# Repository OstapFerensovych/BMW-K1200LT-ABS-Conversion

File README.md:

# BMW K1200LT iABS to iABS gen 2 Conversion PCB and Firmware.

To retrofit BMW K1200LT motorcycle we used the ATE/Teves iABS-II module from 2010 R1200GS K25.  
iABS-II uses CAN bus to communicate with ZFE, DME modules in the original R1200GS schematic.  

This project is developed to provide K1200LT necessary signals from ATE/Teves iABS-II CAN bus:
- Speed signal for K1200LT dash
- Brake and tail lights output
- ABS warning LED output
- General warning LED output  

<!-- 

 -->

## Other resources. 
[Shematics](docs/)

#### PCB is designed in KiCAD 5.1.9

## License

MIT

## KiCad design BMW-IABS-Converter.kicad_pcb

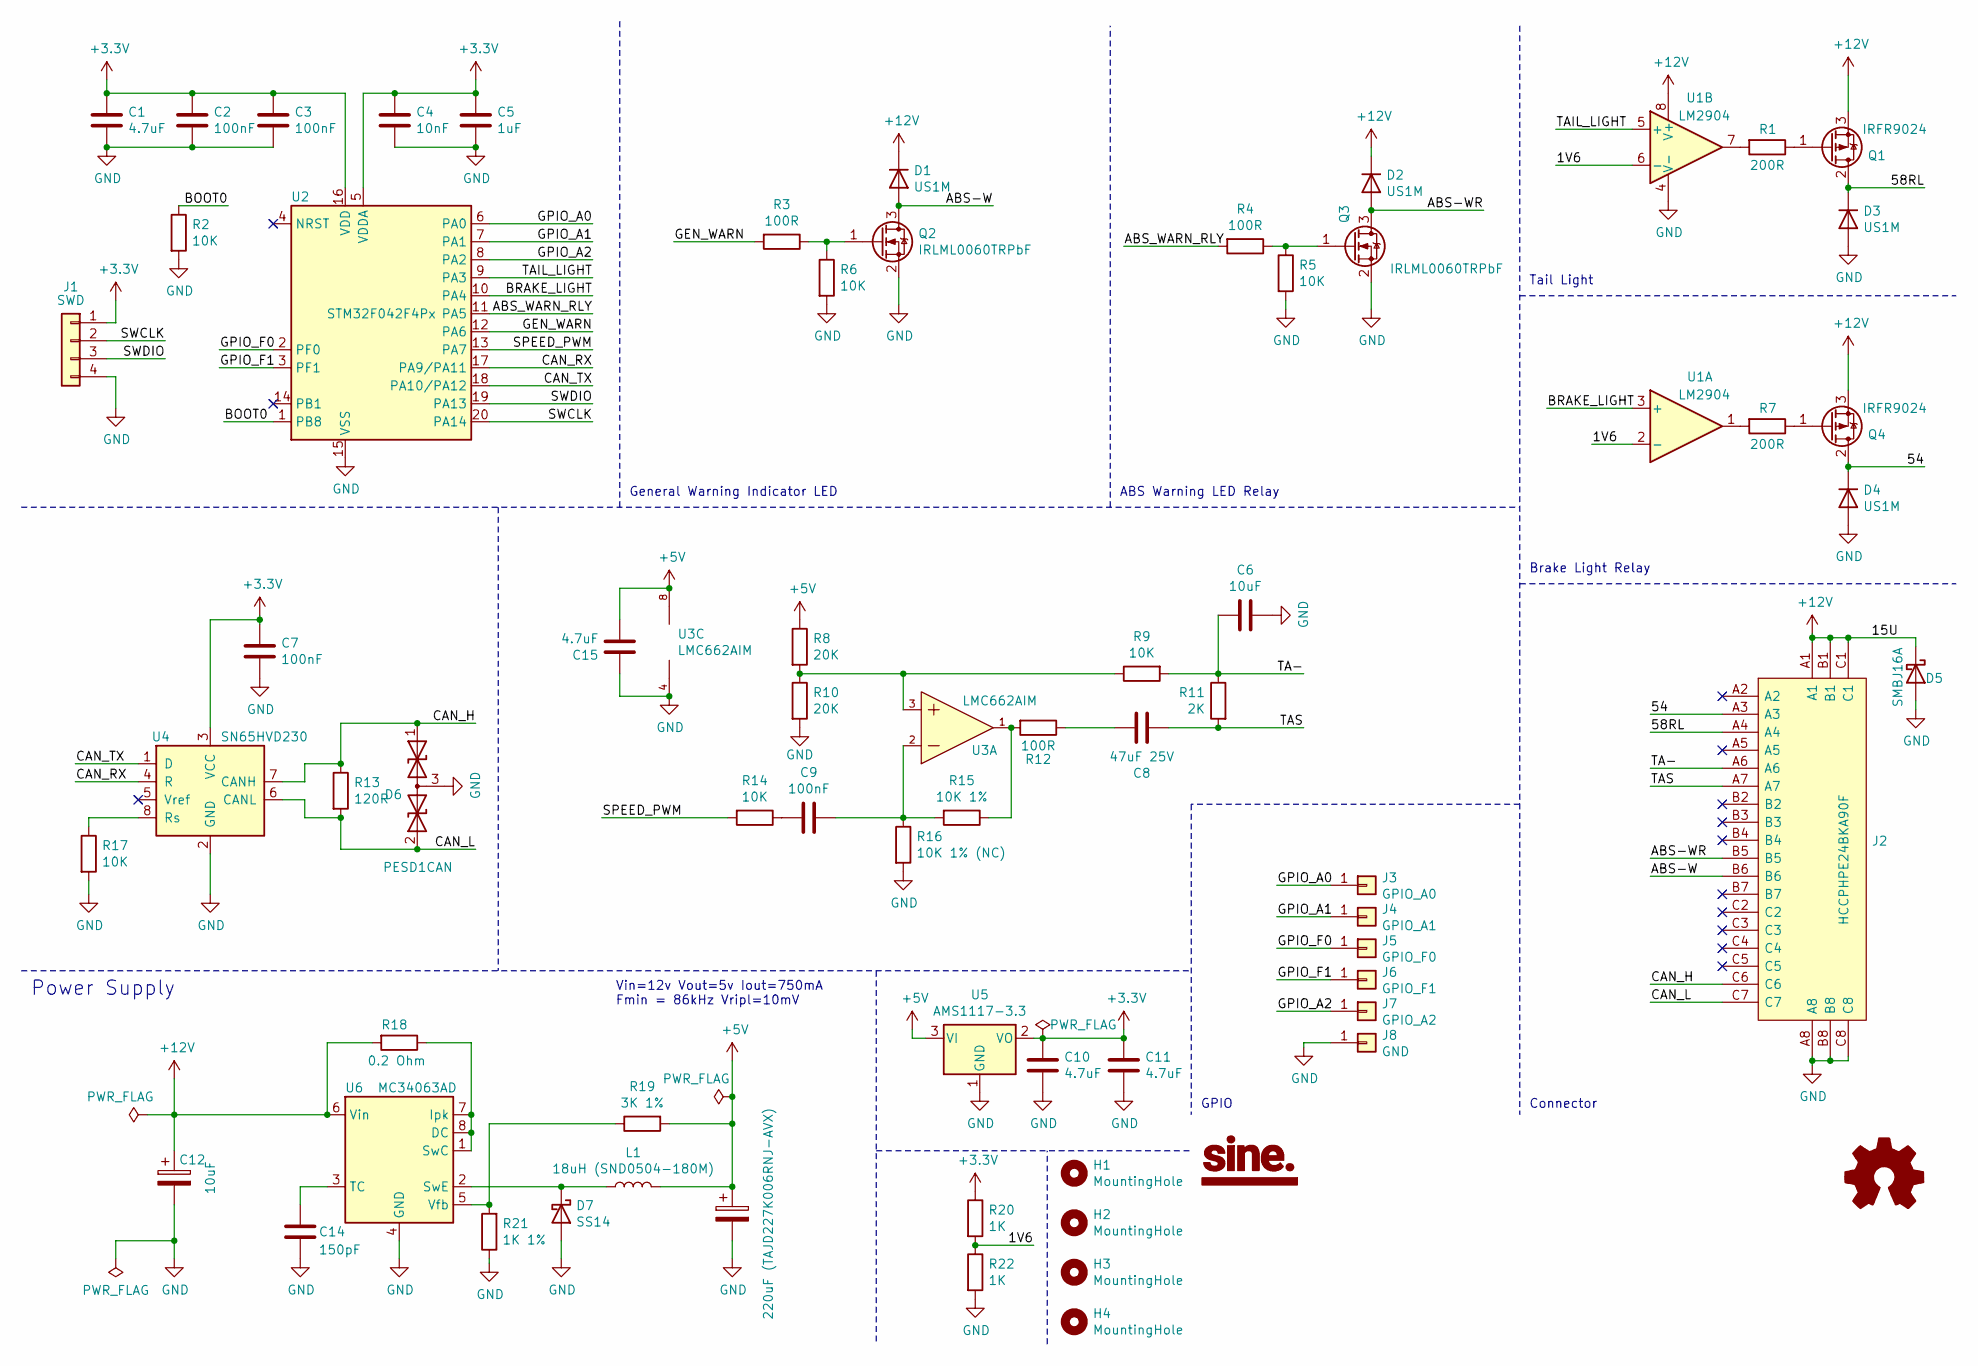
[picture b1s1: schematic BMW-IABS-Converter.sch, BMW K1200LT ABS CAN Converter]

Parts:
C1, C10, C11, C15: 4.7uF; C_0805_2012Metric
C2, C3, C7, C9: 100nF; C_0402_1005Metric
C4: 10nF; C_0402_1005Metric
C5: 1uF; C_0603_1608Metric
C6: 10uF; C_0805_2012Metric
C8: 47uF 25V; C_Radial_D6.3mm_H11.0mm_P2.50mm
C12: 10uF; C_1206_3216Metric
C13: 220uF (TAJD227K006RNJ-AVX); CP_EIA-7343-31_Kemet-D
C14: 150pF; C_0402_1005Metric
D1, D2, D3, D4: US1M; D_SMA
D5: SMBJ16A; D_SMB
D6: PESD1CAN; SOT-23
D7: SS14; D_SMA
H1, H2, H3, H4: MountingHole; MountingHole_3.2mm_M3
J1: SWD; PinHeader_1x04_P2.54mm_Vertical
J2: HCCPHPE24BKA90F; Manufacturer_Part_Number HCCPHPE24BKA90F
J3: GPIO_A0; PinHeader_1x01_P1.27mm_Vertical
J4: GPIO_A1; PinHeader_1x01_P1.27mm_Vertical
J5: GPIO_F0; PinHeader_1x01_P1.27mm_Vertical
J6: GPIO_F1; PinHeader_1x01_P1.27mm_Vertical
J7: GPIO_A2; PinHeader_1x01_P1.27mm_Vertical
J8: GND; PinHeader_1x01_P1.27mm_Vertical
L1: 18uH (SND0504-180M); L_Wuerth_WE-PD2-Typ-MS
LOGO1: Sine_Logo_S; sine_logo_small
LOGO2: Logo_Open_Hardware_Small; OSHW-Symbol_6.7x6mm_SilkScreen
Q1, Q4: IRFR9024; TO-252-2
Q2, Q3: IRLML0060TRPbF; SOT-23
R1, R7: 200R; R_0603_1608Metric
R2, R5, R6, R14, R17: 10K; R_0402_1005Metric
R3, R4, R12: 100R; R_0402_1005Metric
R8, R10: 20K; R_0603_1608Metric
R9: 10K; R_1206_3216Metric
R11: 2K; R_1206_3216Metric
R13: 120R; R_0603_1608Metric
R15: 10K 1%; R_0402_1005Metric
R16: 10K 1% (NC); R_0402_1005Metric
R18: 0.2 Ohm; R_0603_1608Metric
R19: 3K 1%; R_0603_1608Metric
R20, R22: 1K; R_0805_2012Metric
R21: 1K 1%; R_0603_1608Metric
U1: LM2904; SOIC-8_3.9x4.9mm_P1.27mm
U2: STM32F042F4Px; TSSOP-20_4.4x6.5mm_P0.65mm
U3: LMC662AIM; SOIC-8_3.9x4.9mm_P1.27mm
U4: SN65HVD230; SOIC-8_3.9x4.9mm_P1.27mm
U5: AMS1117-3.3; SOT-223-3_TabPin2
U6: MC34063AD; SOIC-8_3.9x4.9mm_P1.27mm

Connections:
+3V3: C1.1, C2.1, C3.1, C4.1, C5.1, C7.1, C10.1, C11.1, J1.1, R20.1, U2.5 (VDDA), U2.16 (VDD), U4.3 (VCC), U5.2 (VO)
+5V: C13.1, C15.2, L1.2, R8.1, R19.2, U3.8 (V+), U5.3 (VI)
+12V: C12.1, D1.1 (K), D2.1 (K), D5.1 (K), J2.A1, J2.B1, J2.C1, Q1.3 (S), Q4.3 (S), R18.2, U1.8 (V+), U6.6 (Vin)
/1V6: R20.2, R22.1, U1.2 (-), U1.6 (-)
/54: D4.1 (K), J2.A3, Q4.2 (D)
/58RL: D3.1 (K), J2.A4, Q1.2 (D)
/ABS-W: D1.2 (A), J2.B6, Q2.3 (D)
/ABS-WR: D2.2 (A), J2.B5, Q3.3 (D)
/ABS_WARN_RLY: R4.2, U2.11 (PA5)
/BOOT0: R2.1, U2.1 (PB8)
/BRAKE_LIGHT: U1.3 (+), U2.10 (PA4)
/CAN_H: D6.1 (A1), J2.C6, R13.1, U4.7 (CANH)
/CAN_L: D6.2 (A2), J2.C7, R13.2, U4.6 (CANL)
/CAN_RX: U2.17 (PA9/PA11), U4.4 (R)
/CAN_TX: U2.18 (PA10/PA12), U4.1 (D)
/GEN_WARN: R3.2, U2.12 (PA6)
/GPIO_A0: J3.1, U2.6 (PA0)
/GPIO_A1: J4.1, U2.7 (PA1)
/GPIO_A2: J7.1, U2.8 (PA2)
/GPIO_F0: J5.1, U2.2 (PF0)
/GPIO_F1: J6.1, U2.3 (PF1)
/SPEED_PWM: R14.2, U2.13 (PA7)
/SWCLK: J1.2, U2.20 (PA14)
/SWDIO: J1.3, U2.19 (PA13)
/TA-: C6.2, J2.A6, R9.2, R11.1
/TAIL_LIGHT: U1.5 (+), U2.9 (PA3)
/TAS: C8.1, J2.A7, R11.2
GND: C1.2, C2.2, C3.2, C4.2, C5.2, C6.1, C7.2, C10.2, C11.2, C12.2, C13.2, C14.2, C15.1, D3.2 (A), D4.2 (A), D5.2 (A), D6.3 (common), D7.2 (A), J1.4, J2.A8, J2.B8, J2.C8, J8.1, Q2.2 (S), Q3.2 (S), R2.2, R5.2, R6.2, R10.2, R16.2, R17.2, R21.1, R22.2, U1.4 (V-), U2.15 (VSS), U3.4 (V-), U4.2 (GND), U5.1 (GND), U6.4 (GND)
unnamed: C8.2, R12.1
unnamed: C9.1, R15.2, R16.1, U3.2 (INA-)
unnamed: C9.2, R14.1
unnamed: C14.1, U6.3 (TC)
unnamed: D7.1 (K), L1.1, U6.2 (SwE)
unnamed: Q1.1 (G), R1.1
unnamed: Q2.1 (G), R3.1, R6.1
unnamed: Q3.1 (G), R4.1, R5.1
unnamed: Q4.1 (G), R7.1
unnamed: R1.2, U1.7
unnamed: R7.2, U1.1
unnamed: R8.2, R9.1, R10.1, U3.3 (INA+)
unnamed: R12.2, R15.1, U3.1 (OUTA)
unnamed: R17.1, U4.8 (Rs)
unnamed: R18.1, U6.1 (SwC), U6.7 (Ipk), U6.8 (DC)
unnamed: R19.1, R21.2, U6.5 (Vfb)

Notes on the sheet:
Power Supply
Vin=12v Vout=5v Iout=750mA Fmin = 86kHz Vripl=10mV
ABS Warning LED Relay
General Warning Indicator LED
Brake Light Relay
Tail Light
Connector
GPIO

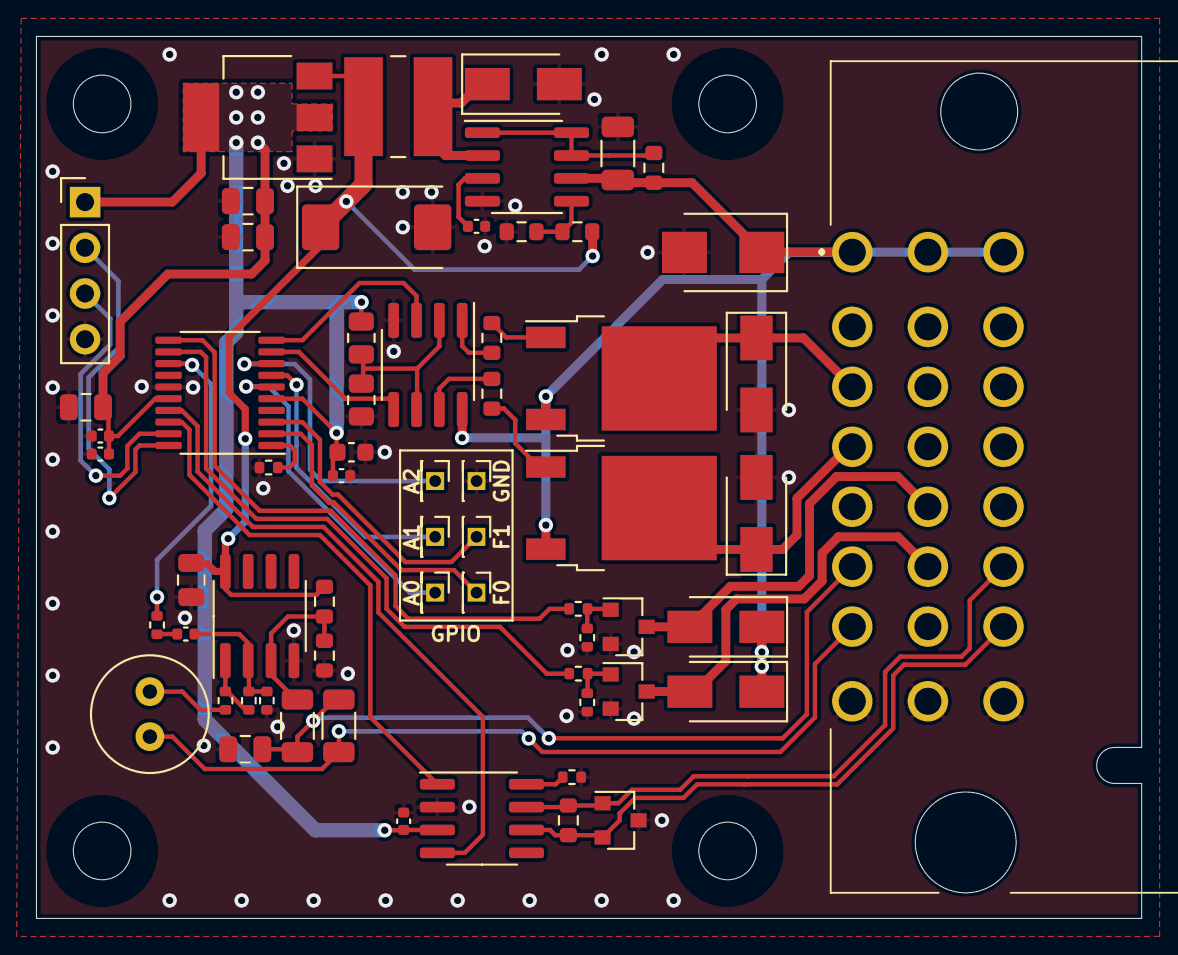
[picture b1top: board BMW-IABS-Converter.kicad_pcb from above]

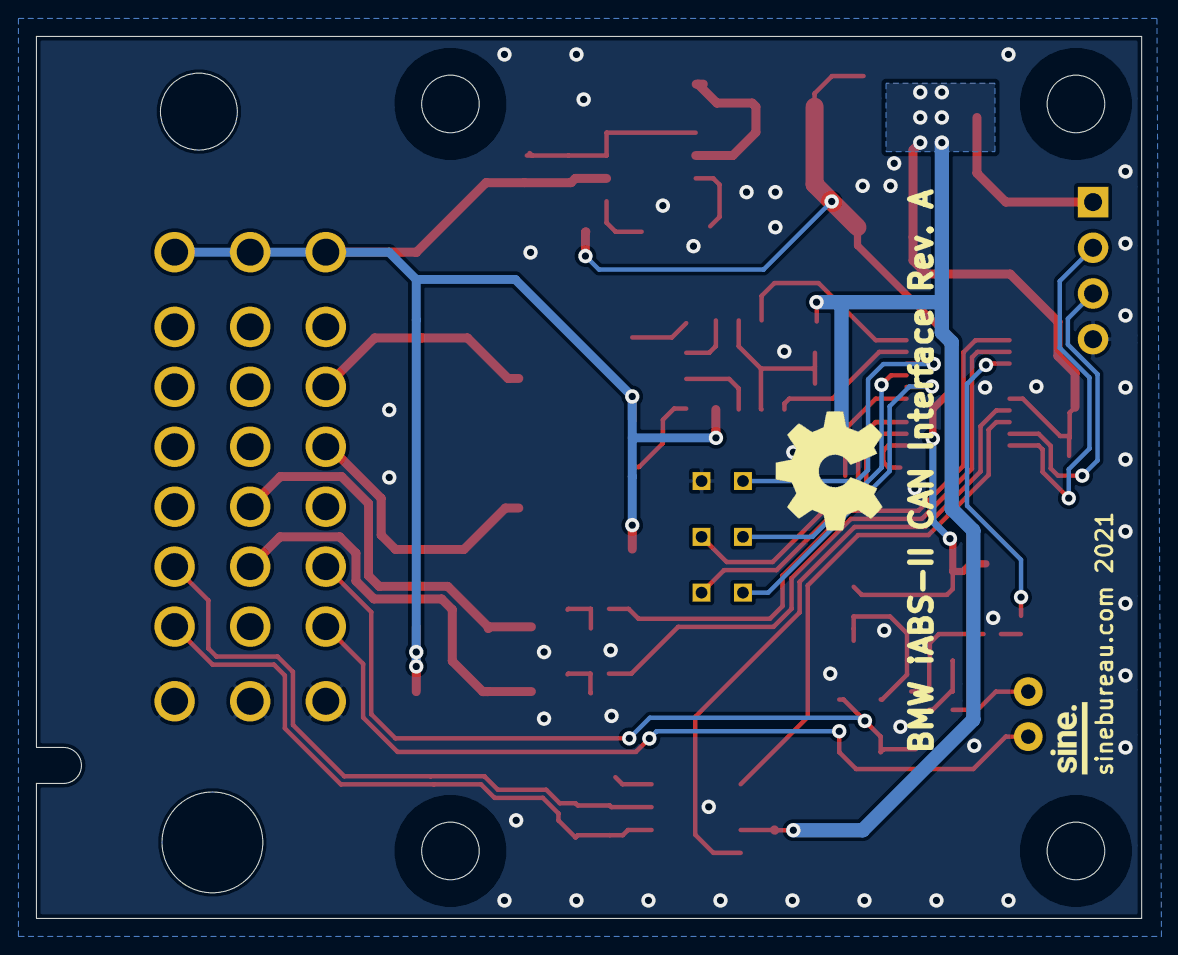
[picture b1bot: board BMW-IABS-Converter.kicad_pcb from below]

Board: 2 copper layers, 61.4 x 49.0 mm, 69 parts (2 on the bottom side), 44 nets.

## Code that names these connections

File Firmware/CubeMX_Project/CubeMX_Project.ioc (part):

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Mcu.Name=STM32F042F4Px
Mcu.Package=TSSOP20
Mcu.UserName=STM32F042F4Px
PA0.Signal=GPIO_Output
PA1.Signal=GPIO_Output
PA11.Mode=CAN_Activate
PA11.Signal=CAN_RX
PA12.Mode=CAN_Activate
PA12.Signal=CAN_TX
PA13.Mode=Serial_Wire
PA13.Signal=SYS_SWDIO
PA14.Mode=Serial_Wire
PA14.Signal=SYS_SWCLK
PA2.Signal=GPIO_Output
PA3.GPIOParameters=GPIO_Label
PA3.GPIO_Label=Tail_light
PA3.Signal=GPIO_Output
PA4.GPIOParameters=GPIO_Label
PA4.GPIO_Label=Brake_light
PA4.Signal=GPIO_Output
PA5.GPIOParameters=GPIO_Label
PA5.GPIO_Label=ABS_Warn_RLY
PA5.Signal=GPIO_Output
PA6.GPIOParameters=GPIO_Label
PA6.GPIO_Label=Gen_warn
PA6.Signal=GPIO_Output
PA7.GPIOParameters=GPIO_Label
PA7.GPIO_Label=Speedo
PA7.Signal=S_TIM3_CH2
PF0-OSC_IN.Signal=GPIO_Output
PF1-OSC_OUT.Signal=GPIO_Output
board=custom

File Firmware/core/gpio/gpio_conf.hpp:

#pragma once
#include "gpio.hpp"

enum class line {
    __invalid__,
    can_rx,
    can_tx,
    speedo,
    gen_warn,
    abs_warn_relay,
    brake_lights,
    tail_lights,
    gpio_A0,
    gpio_A1,
    gpio_A2,
    gpio_F0,
    gpio_F1
};

// clang-format off
constexpr std::pair<line, gpio::pin_config> pins_config[] = {
    {line::can_rx,         {gpio::port::a, 11, 0, gpio::mode::af_io, gpio::drive::push_pull, gpio::speed::high, gpio::pull::none, gpio::alt_func::af4}},
    {line::can_tx,         {gpio::port::a, 12, 0, gpio::mode::af_io, gpio::drive::push_pull, gpio::speed::high, gpio::pull::none, gpio::alt_func::af4}},
    {line::speedo,         {gpio::port::a, 7, 0,  gpio::mode::af_io,  gpio::drive::push_pull, gpio::speed::high, gpio::pull::none, gpio::alt_func::af1 }},
    {line::gen_warn,       {gpio::port::a, 6, 0,  gpio::mode::gp_out,  gpio::drive::push_pull, gpio::speed::low, gpio::pull::none, gpio::alt_func::none }},
    {line::abs_warn_relay, {gpio::port::a, 5, 1,  gpio::mode::gp_out,  gpio::drive::push_pull, gpio::speed::low, gpio::pull::none, gpio::alt_func::none }},
    {line::brake_lights,   {gpio::port::a, 4, 1,  gpio::mode::gp_out,  gpio::drive::push_pull, gpio::speed::low, gpio::pull::none, gpio::alt_func::none }},
    {line::tail_lights,    {gpio::port::a, 3, 1,  gpio::mode::gp_out,  gpio::drive::push_pull, gpio::speed::low, gpio::pull::none, gpio::alt_func::none }},
    {line::gpio_A0,        {gpio::port::a, 0, 0,  gpio::mode::gp_out,  gpio::drive::push_pull, gpio::speed::low, gpio::pull::none, gpio::alt_func::none }},
    {line::gpio_A1,        {gpio::port::a, 1, 0,  gpio::mode::gp_out,  gpio::drive::push_pull, gpio::speed::low, gpio::pull::none, gpio::alt_func::none }},
    {line::gpio_A2,        {gpio::port::a, 2, 0,  gpio::mode::gp_out,  gpio::drive::push_pull, gpio::speed::low, gpio::pull::none, gpio::alt_func::none }},
    {line::gpio_F0,        {gpio::port::f, 0, 0,  gpio::mode::gp_out,  gpio::drive::push_pull, gpio::speed::low, gpio::pull::none, gpio::alt_func::none }},
    {line::gpio_F1,        {gpio::port::f, 1, 0,  gpio::mode::gp_out,  gpio::drive::push_pull, gpio::speed::low, gpio::pull::none, gpio::alt_func::none }},
};
// clang-format on

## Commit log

2021-02-20 Added README
2021-02-20 Updated docs
2021-02-20 Added wiring diagrams
2021-02-20 Updated schematics
2021-02-20 Fixed schematics
2021-02-20 Added connector footprint and symbol
2021-02-21 Added connector 3D model
2021-02-21 Updated footprint and layout
2021-02-21 Create LICENSE
2021-02-21 Added misc libs
2021-02-21 Added coil 3D model
2021-02-21 Updated .gitignore and .gitattributes files
2021-02-21 Cleanup
2021-02-21 Updated schematic and layout
2021-02-21 Added PCB renders
2021-02-22 Updated coil 3d model
2021-02-22 Added pdf version of schematic
2021-02-22 Changed MOSFETS to 0030
2021-02-22 Updated schematic
2021-04-16 Reverse engineering FTE ABS tacho output
2021-06-10 Updated the PDF version of schematic
2021-06-29 Fixed mcu package.
2021-08-05 Refactoring repository
2021-08-05 Firmware initial commit
2021-08-05 More refactoring
2021-08-08 Added CAN messages parsing and handling outputs
2021-08-16 Ignore .d .o
2021-08-16 Added ABS ON/OFF Status tracking
2021-08-18 Added rear abs status message handling and etc.
2021-08-18 Added Case files
2021-08-19 Added rear ABS ring and ABS sensor bracket files
